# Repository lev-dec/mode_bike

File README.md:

# mode_bike
 Design of a bike PCB

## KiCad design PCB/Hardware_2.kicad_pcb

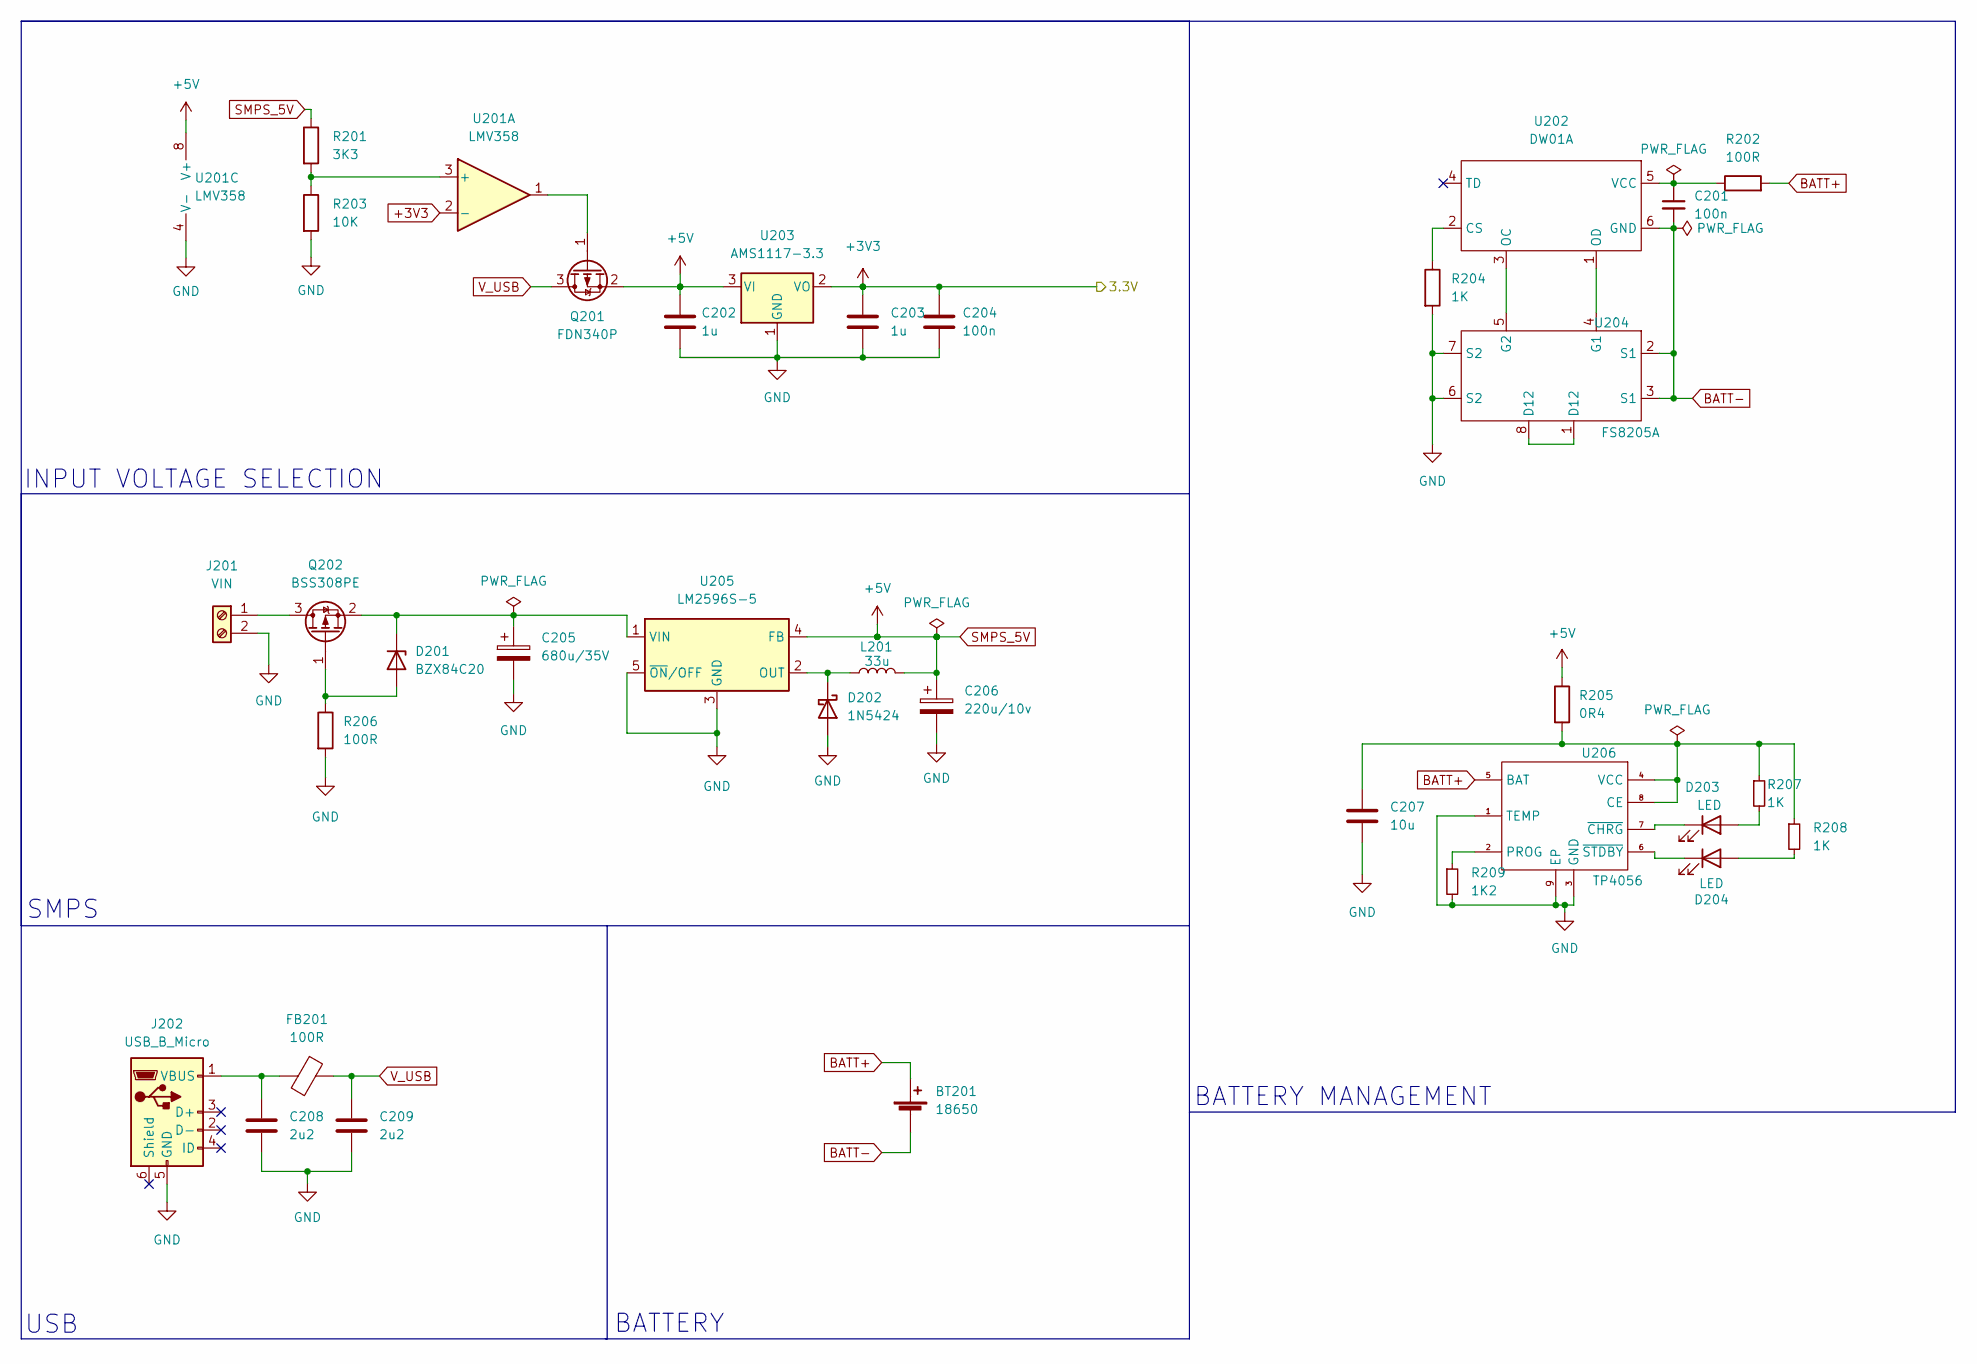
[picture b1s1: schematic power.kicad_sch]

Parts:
BT201: 18650; BatteryHolder_MPD_BH-18650-PC2
C201, C204: 100n; C_0402_1005Metric
C202, C203: 1u; C_0603_1608Metric
C205: 680u/35V; C_0603_1608Metric
C206: 220u/10v; C_0603_1608Metric
C207: 10u; C_0603_1608Metric
C208, C209: 2u2; C_0603_1608Metric
D201: BZX84C20; SOT-23
D202: 1N5424; D_0603_1608Metric
D203, D204: LED; LED_0603_1608Metric
FB201: 100R; LED_0603_1608Metric
J201: VIN; PinHeader_1x02_P2.54mm_Vertical
J202: USB_B_Micro; USB_Micro-B_Molex_47346-0001
L201: 33u; L_0603_1608Metric
Q201: FDN340P; SOT-23
Q202: BSS308PE; SOT-23
R201: 3K3; R_0603_1608Metric
R202, R206: 100R; R_0603_1608Metric
R203: 10K; R_0603_1608Metric
R204, R207, R208: 1K; R_0603_1608Metric
R205: 0R4; R_0603_1608Metric
R209: 1K2; R_0603_1608Metric
U201: LMV358; SOT-23
U202: DW01A; TSOP-6_1.65x3.05mm_P0.95mm
U203: AMS1117-3.3; SOT-223-3_TabPin2
U204: FS8205A; TSSOP-8_3x3mm_P0.65mm
U205: LM2596S-5; TO-263-5_TabPin3
U206: TP4056; SOP-8_6.62x9.15mm_P2.54mm

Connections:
+3V3: C203.1, C204.1, U201.2 (-), U203.2 (VO); also elsewhere on the board
BATT+: BT201.1 (+), R202.2, U206.5 (BAT)
BATT-: BT201.2 (-), C201.2, U202.6 (GND), U204.2 (S1), U204.3 (S1)
GND: C202.2, C203.2, C204.2, C205.2, C206.2, C207.2, C208.2, C209.2, D202.2 (A), J201.2, J202.5 (GND), R203.2, R204.2, R206.2, R209.2, U201.4 (V-), U203.1 (GND), U204.6 (S2), U204.7 (S2), U205.3 (GND), U205.5 (~ON/OFF), U206.1 (TEMP), U206.3 (GND), U206.9 (EP); also elsewhere on the board
unnamed: C201.1, R202.1, U202.5 (VCC)
unnamed: C205.1, D201.3 (K), Q202.2 (S), U205.1 (VIN)
unnamed: C207.1, R205.2, R207.1, R208.1, U206.4 (VCC), U206.8 (CE)
unnamed: C208.1, FB201.2, J202.1 (VBUS)
unnamed: D201.1 (A), Q202.1 (G), R206.1
unnamed: D202.1 (K), L201.1, U205.2 (OUT)
unnamed: D203.1 (K), U206.7 (~CHRG)
unnamed: D203.2 (A), R207.2
unnamed: D204.1 (K), U206.6 (~STDBY)
unnamed: D204.2 (A), R208.2
unnamed: J201.1, Q202.3 (D)
unnamed: Q201.1 (G), U201.1
unnamed: R201.2, R203.1, U201.3 (+)
unnamed: R204.1, U202.2 (CS)
unnamed: R209.1, U206.2 (PROG)
unnamed: U202.1 (OD), U204.4 (G1)
unnamed: U202.3 (OC), U204.5 (G2)
unnamed: U204.1 (D12), U204.8 (D12)
SMPS_5V: C202.1, C206.1, L201.2, Q201.2 (S), R201.1, R205.1, U201.8 (V+), U203.3 (VI), U205.4 (FB)
V_USB: C209.1, FB201.1, Q201.3 (D)

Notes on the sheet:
INPUT VOLTAGE SELECTION
BATTERY MANAGEMENT
USB
SMPS
BATTERY

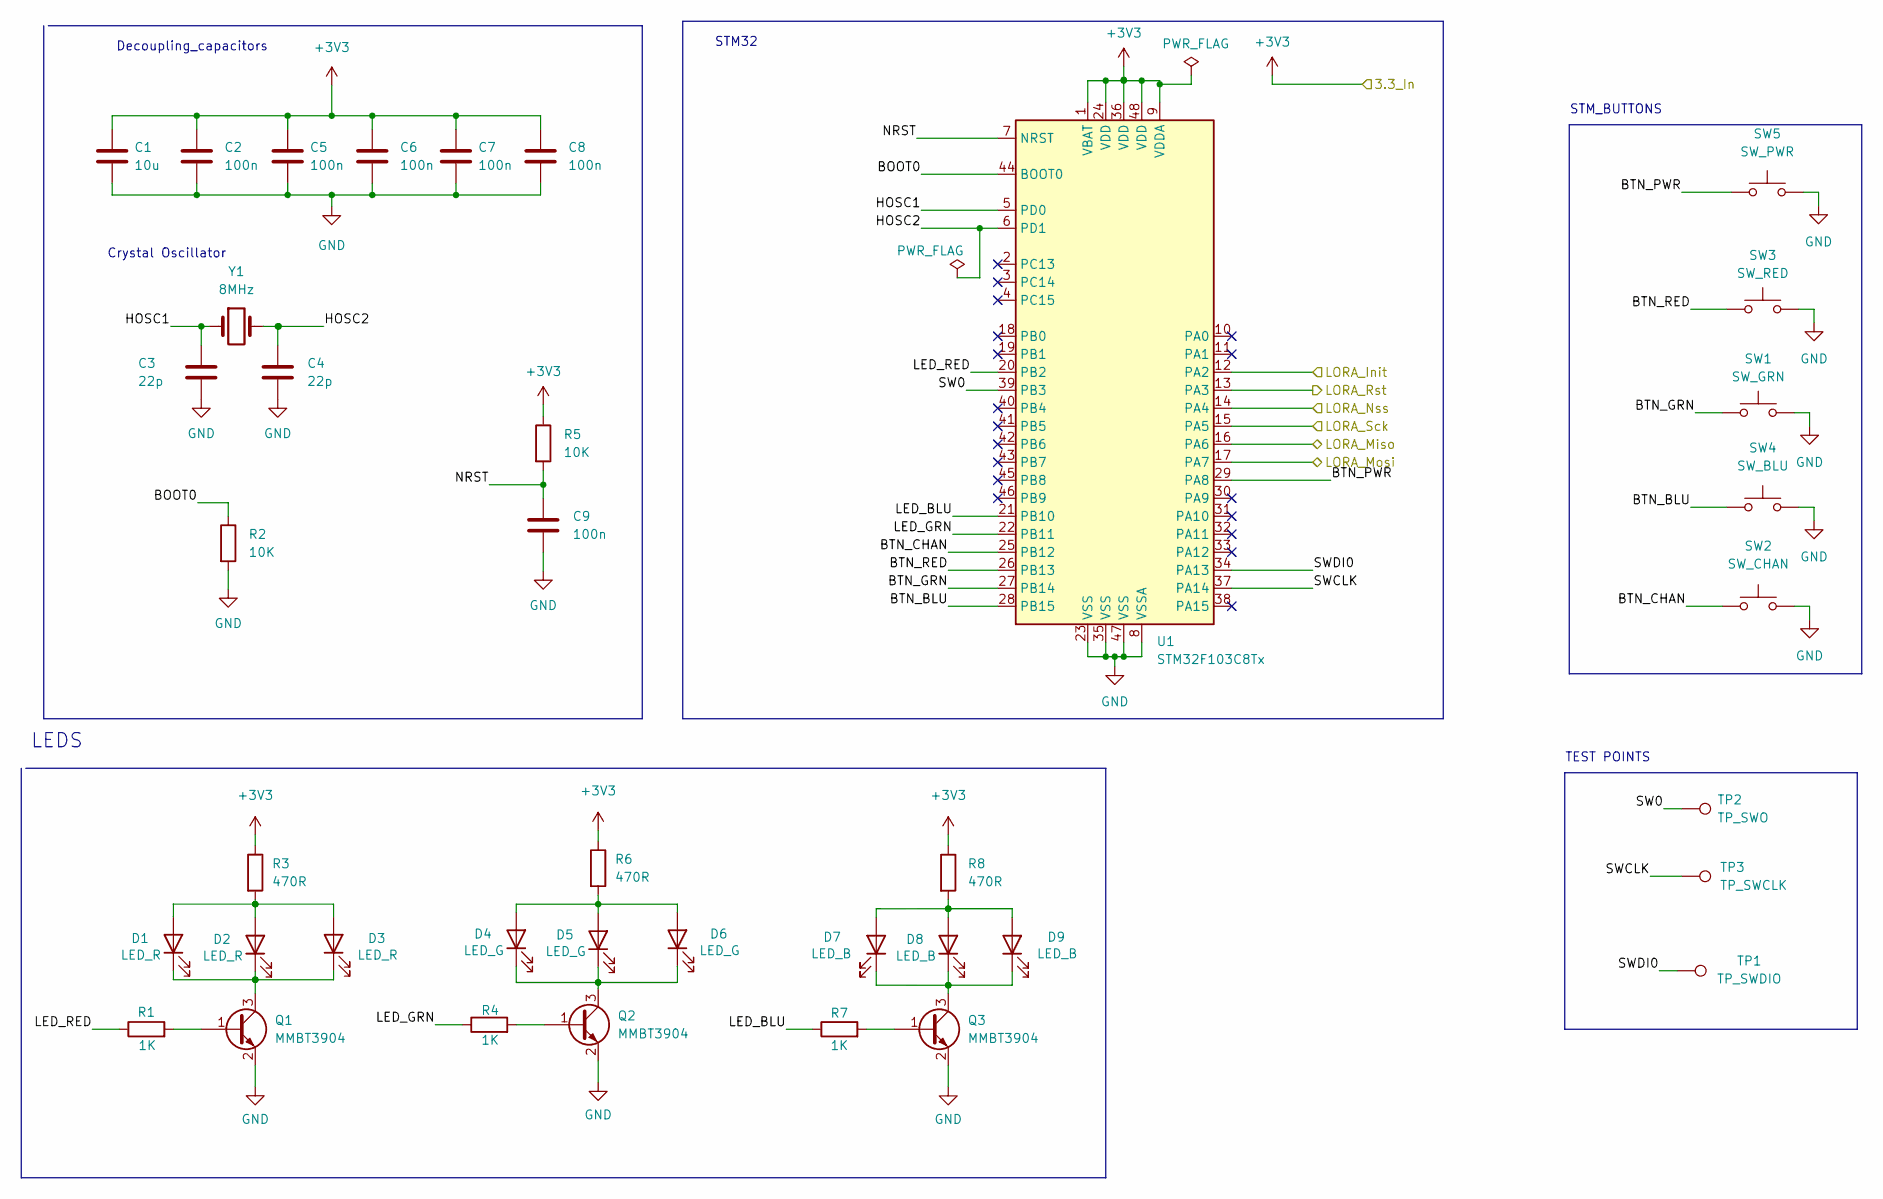
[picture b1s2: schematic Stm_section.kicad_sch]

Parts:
C1: 10u; C_0603_1608Metric
C2, C5, C6, C7, C8, C9: 100n; C_0402_1005Metric
C3: 22p; C_0402_1005Metric_Pad0.74x0.62mm_HandSolder
C4: 22p; C_0402_1005Metric
D1, D2, D3: LED_R; LED_0603_1608Metric
D4, D5, D6: LED_G; LED_0603_1608Metric
D7, D8, D9: LED_B; LED_0603_1608Metric
Q1, Q2, Q3: MMBT3904; SOT-23
R1, R4, R7: 1K; R_0603_1608Metric
R2, R5: 10K; R_0603_1608Metric
R3, R6, R8: 470R; R_0603_1608Metric
SW1: SW_GRN; SW_SPST_TL3342
SW2: SW_CHAN; SW_SPST_TL3342
SW3: SW_RED; SW_SPST_TL3342
SW4: SW_BLU; SW_SPST_TL3342
SW5: SW_PWR; SW_SPST_TL3342
TP1: TP_SWDIO; TestPoint_Pad_D2.0mm
TP2: TP_SWO; TestPoint_Pad_D2.0mm
TP3: TP_SWCLK; TestPoint_Pad_D2.0mm
U1: STM32F103C8Tx; LQFP-48_7x7mm_P0.5mm
Y1: 8MHz; Crystal_SMD_0603-4Pin_6.0x3.5mm

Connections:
+3V3: C1.1, C2.1, C5.1, C6.1, C7.1, C8.1, R3.1, R5.1, R6.1, R8.1; also elsewhere on the board
/LORA/INIT_Lora: U1.12 (PA2); also elsewhere on the board
/LORA/Miso_LORA: U1.16 (PA6); also elsewhere on the board
/LORA/Mosi_LORA: U1.17 (PA7); also elsewhere on the board
/LORA/NSS_lora: U1.14 (PA4); also elsewhere on the board
/LORA/RST_Lora: U1.13 (PA3); also elsewhere on the board
/LORA/SCK: U1.15 (PA5); also elsewhere on the board
/STM32/BOOT0: R2.1, U1.44 (BOOT0)
/STM32/BTN_BLU: SW4.1, U1.28 (PB15)
/STM32/BTN_CHAN: SW2.1, U1.25 (PB12)
/STM32/BTN_GRN: SW1.1, U1.27 (PB14)
/STM32/BTN_PWR: SW5.1, U1.29 (PA8)
/STM32/BTN_RED: SW3.1, U1.26 (PB13)
/STM32/HOSC1: C3.1, U1.5 (PD0), Y1.1
/STM32/HOSC2: U1.6 (PD1)
/STM32/LED_BLU: R7.1, U1.21 (PB10)
/STM32/LED_GRN: R4.1, U1.22 (PB11)
/STM32/LED_RED: R1.1, U1.20 (PB2)
/STM32/NRST: C9.1, R5.2, U1.7 (NRST)
/STM32/SW0: TP2.1, U1.39 (PB3)
/STM32/SWCLK: TP3.1, U1.37 (PA14)
/STM32/SWDI0: TP1.1, U1.34 (PA13)
GND: C1.2, C2.2, C3.2, C4.2, C5.2, C6.2, C7.2, C8.2, C9.2, Q1.2 (E), Q2.2 (E), Q3.2 (E), R2.2, SW1.2, SW2.2, SW3.2, SW4.2, SW5.2, U1.8 (VSSA), U1.23 (VSS), U1.35 (VSS), U1.47 (VSS); also elsewhere on the board
unnamed: C4.1, Y1.2
unnamed: D1.1 (K), D2.1 (K), D3.1 (K), Q1.3 (C)
unnamed: D1.2 (A), D2.2 (A), D3.2 (A), R3.2
unnamed: D4.1 (K), D5.1 (K), D6.1 (K), Q2.3 (C)
unnamed: D4.2 (A), D5.2 (A), D6.2 (A), R6.2
unnamed: D7.1 (K), D8.1 (K), D9.1 (K), Q3.3 (C)
unnamed: D7.2 (A), D8.2 (A), D9.2 (A), R8.2
unnamed: Q1.1 (B), R1.2
unnamed: Q2.1 (B), R4.2
unnamed: Q3.1 (B), R7.2
unnamed: U1.1 (VBAT), U1.9 (VDDA), U1.24 (VDD), U1.36 (VDD), U1.48 (VDD)

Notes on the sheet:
TEST POINTS
STM_BUTTONS
STM32
Decoupling_capacitors
LEDS
Crystal Oscillator

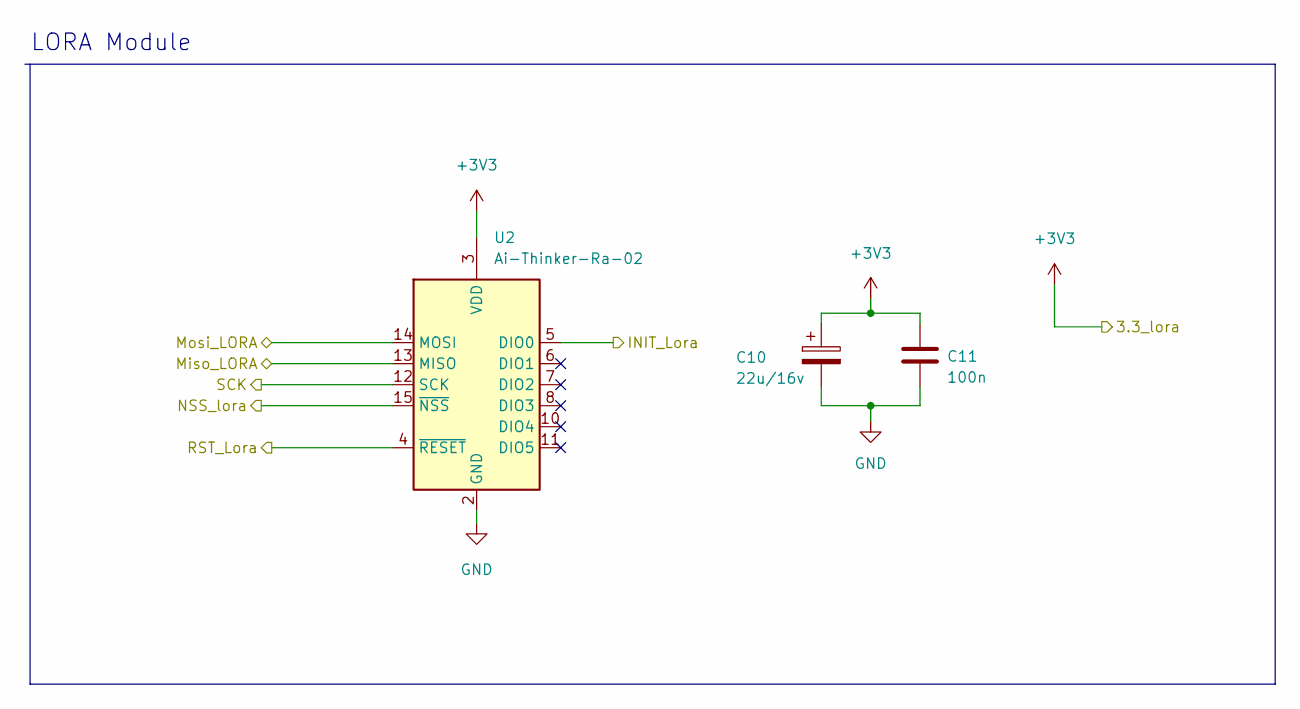
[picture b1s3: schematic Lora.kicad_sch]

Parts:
C10: 22u/16v; C_0402_1005Metric
C11: 100n; C_0402_1005Metric
U2: Ai-Thinker-Ra-02; Ai-Thinker-Ra-01-LoRa

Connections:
+3V3: C10.1, C11.1, U2.3 (VDD); also elsewhere on the board
/LORA/INIT_Lora: U2.5 (DIO0); also elsewhere on the board
/LORA/Miso_LORA: U2.13 (MISO); also elsewhere on the board
/LORA/Mosi_LORA: U2.14 (MOSI); also elsewhere on the board
/LORA/NSS_lora: U2.15 (~NSS); also elsewhere on the board
/LORA/RST_Lora: U2.4 (~RESET); also elsewhere on the board
/LORA/SCK: U2.12 (SCK); also elsewhere on the board
GND: C10.2, C11.2, U2.1 (GND), U2.2 (GND), U2.9 (GND), U2.16 (GND); also elsewhere on the board

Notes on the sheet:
LORA Module

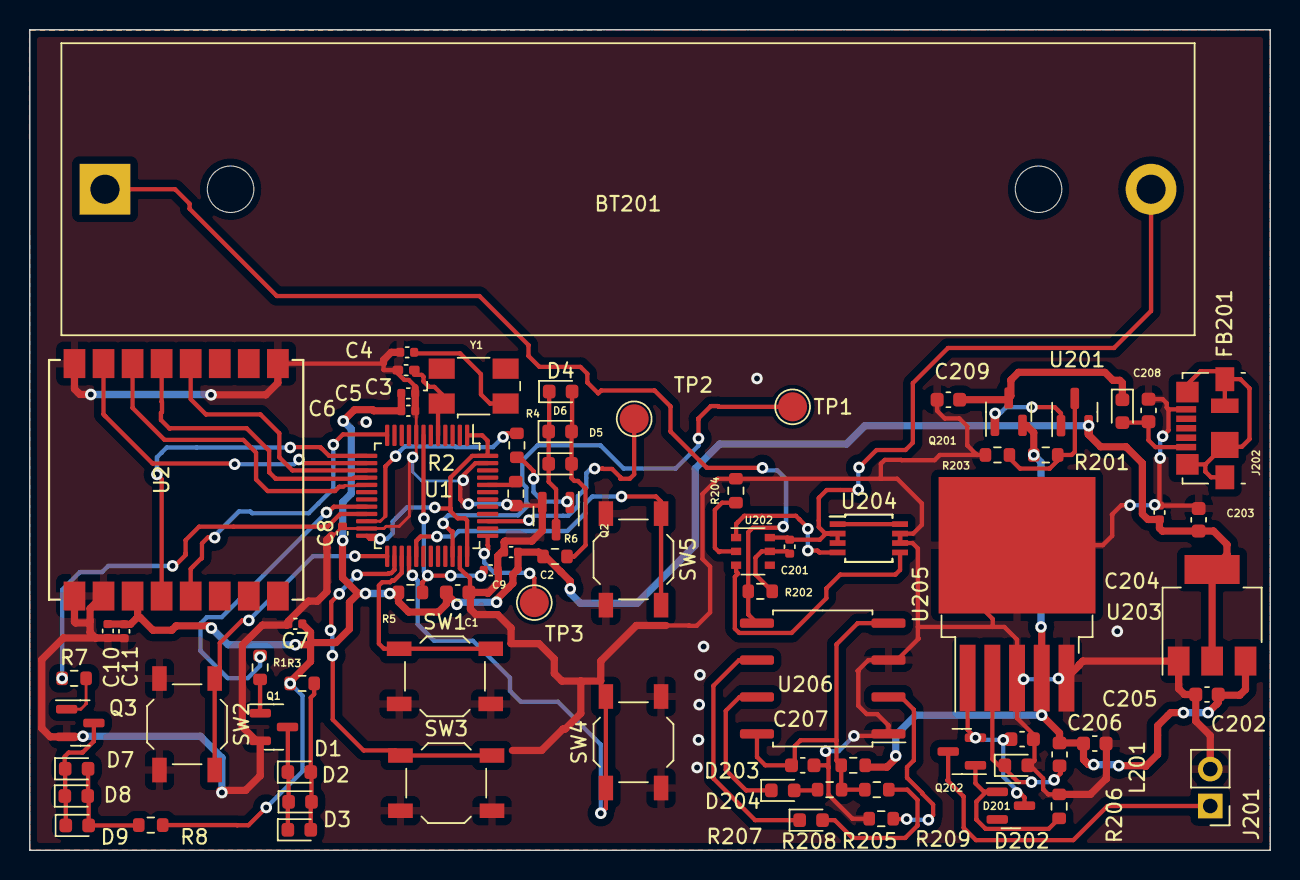
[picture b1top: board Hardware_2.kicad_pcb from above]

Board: 2 copper layers, 85.4 x 56.5 mm, 77 parts (0 on the bottom side), 55 nets.

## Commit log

2022-12-14 1st commit
